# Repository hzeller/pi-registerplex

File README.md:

GPIO Multiplexer with registers
================================

 * 1x32 'raw' output of GPIO pins, or inputs if not used with a Pi
 * 1x32 bit buffer (AHCT245) to buffer all 28 GPIO bits plus 4 user bits
 * 2x32 bit registers (AHCT574) with user-choice of clock.
 * 6 NOT gates that can be used to use as clock inverter and play with gate
   delays.

This board directly plugs into the Rasbperry Pi and can be used as a GPIO
multiplexer with that, but the raw inputs are also available directly, so
this can be used in any project. The 34 pin connectors have the same
pinout throughout: +5V and GND followed by 32 bits of data.

Using the AHCT gates allows to voltage convert 3.3V logic levels to 5V.

The chip packages are [DHVQFN20], which allows for compact design and is
still somewhat easy to solder if you use a stencil.

Chip       | Package              | Vendor type example
-----------|----------------------|---------------
74AHCT245  | DHVQFN20 (SOT764-1)  | NXP 74AHCT245BQ,115
74AHCT574  | DHVQFN20 (SOT764-1)  | NXP 74AHCT574BQ,115
74AHCT04   | DHVQFN14 (SOT762-1)  | NXP 74AHCT04BQ,115

The clocks (`J6` and `J7`) of the registers are not connected by default, so
it allows you to choose any GPIO output or other signal to clock in the
registers.

The buffer and registers are for 32 bits, but we only have 28 GPIO outputs.
The remaining bits are passed through as user bits (`U1` ... `U4`) from inputs
on the `J2` 'Raw' header.

PCB is [shared on OshPark].

### Using two clocks
Pick two GPIO lines as a clock to connect to `J6` and `J7` allows to write
to the registers. Straight forward:

  1. write Datum1, transition clock2 `¯╲_`
  2. transition clock1 `_╱¯`  _(clocks in Datum1)_
  3. Write Datum2, transition clock1 `¯╲_`
  4. transition clock2 `_╱¯`  _(clocks in Datum2)_

In this case, the inverter gates are not needed.

### Using one clock
Chose one GPIO as clock and wire it up to an inverter. Wire up one of the 574's
directly to the pin, and the other through the inverter.

  1. Write Datum1
  2. transition clock `_╱¯` _(clocks in Datum1)_
  3. Write Datum2
  4. transition clock `¯╲_` _(the inverted signal clocks in Datum2)_

Same as above, but only one clock line needed.

### Danger zone: DDR with just two writes

Wire up the `Clock` line to at least one inverters, maybe more in one chain to
create some delay. Let's call this `Clock'`. Take the output of that through
another inverter, let's call this `Clock''`. Connect these to `J6` and `J7`.

 1. Clock in Datum1 and with it transition `Clock` `_╱¯`. The delayed
    clock prime that transitions to positive a few nanoseconds later will
    clock in the data.
 2. Clock in Datum2 and with it transition `Clock` `¯╲_`. The inverted clock
    from (1) now transitions to positive a few nanoseconds later
    will clock in the data.

Each write write will store one datum. Using the gates as
delay line and inverter, no separate cycle is needed, each swing of the
clock generates a store.

This is dangerous of course: it is not necessarily stable as we rely on the
delay to be long enough for the D-FlipFlops set-up time, and this will highly
depend on the chip manufacturer, temperature, age, ...
Maybe use RC + AHCT14 or LV14 Schmitt-Trigger for a more defined delay ?

[DHVQFN20]: https://www.nexperia.com/packages/SOT764-1.html
[shared on OshPark]: https://oshpark.com/shared_projects/xJGfE6Gh

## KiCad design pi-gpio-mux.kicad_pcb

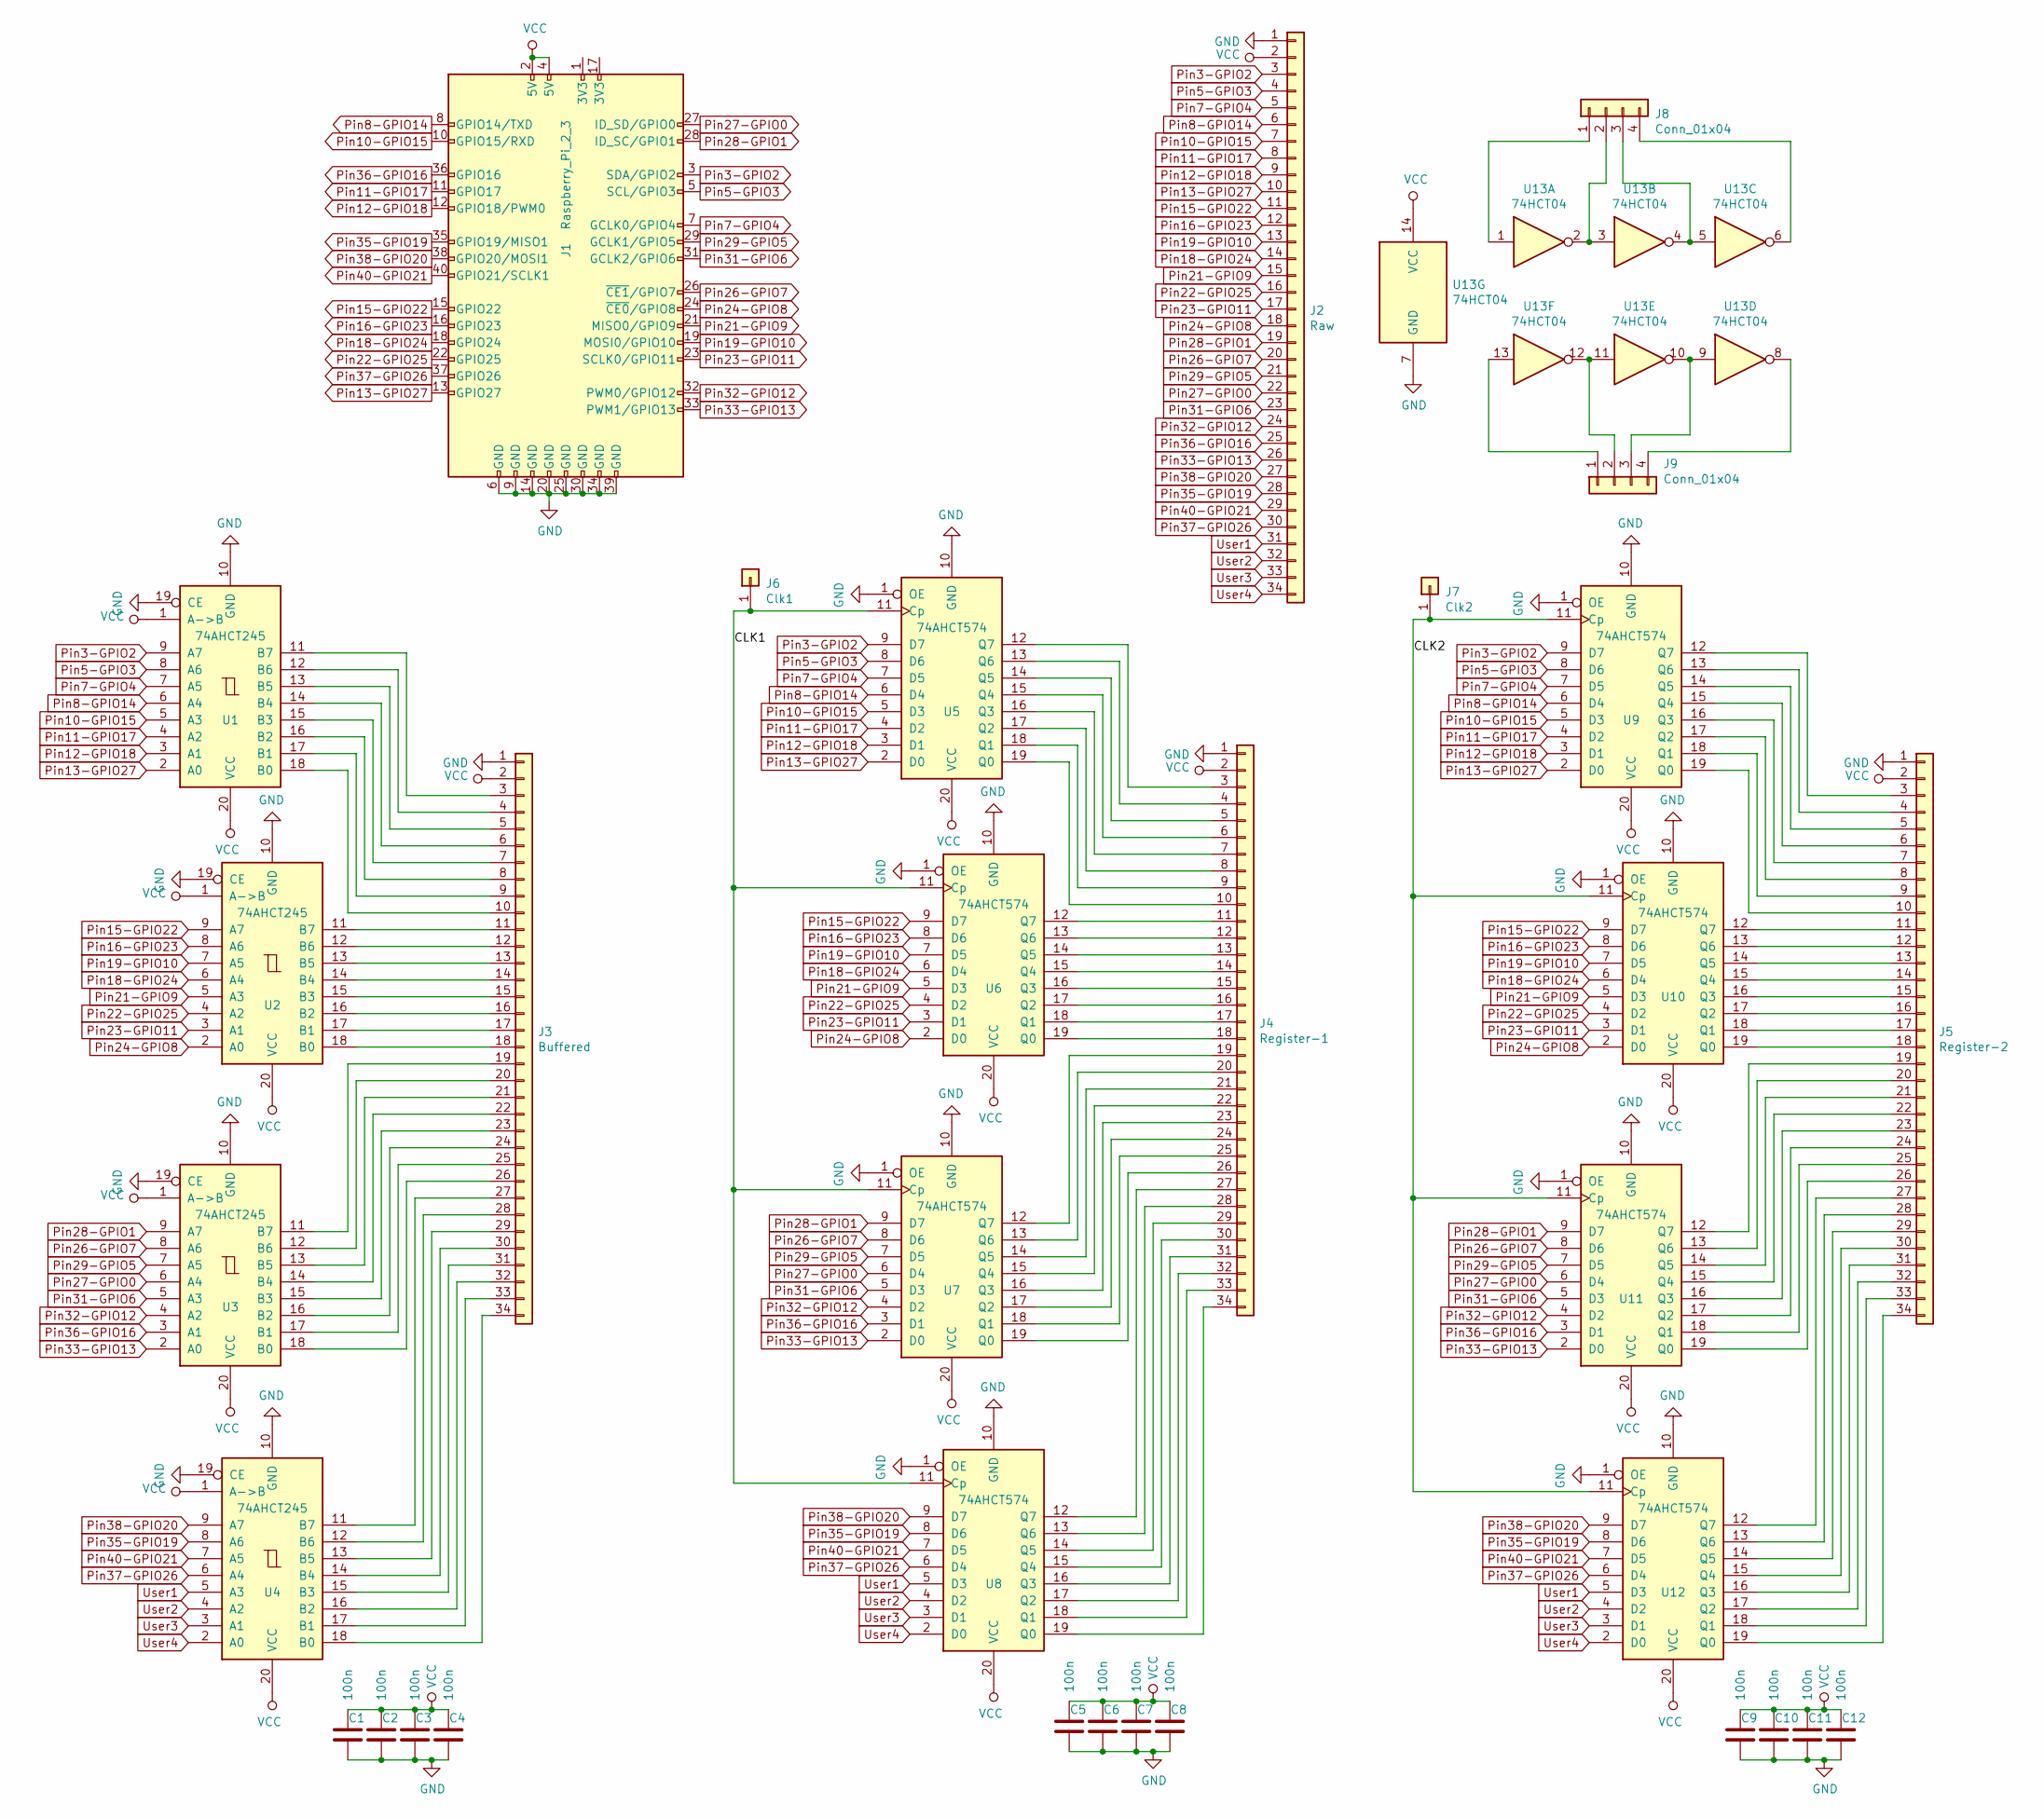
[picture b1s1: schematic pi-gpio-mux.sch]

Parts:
C1, C2, C3, C4, C5, C6, C7, C8, C9, C10, C11, C12: 100n; C_0603_1608Metric
J1: Raspberry_Pi_2_3; PinHeader_2x20_P2.54mm_Vertical
J2: Raw; IDC-GPIO
J3: Buffered; IDC-GPIO
J4: Register-1; IDC-GPIO
J5: Register-2; IDC-GPIO
J6: Clk1; Pin_D0.7mm_L6.5mm_W1.8mm_FlatFork
J7: Clk2; Pin_D0.7mm_L6.5mm_W1.8mm_FlatFork
J8, J9: Conn_01x04; triple-inverter
U1, U2, U3, U4: 74AHCT245; SOT764-1-DHVQFN20
U5, U6, U7, U8, U9, U10, U11, U12: 74AHCT574; SOT764-1-DHVQFN20
U13: 74HCT04; SOT762-1-DHVQFN14

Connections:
/CLK1: J6.1, U5.11 (Cp), U6.11 (Cp), U7.11 (Cp), U8.11 (Cp)
/CLK2: J7.1, U9.11 (Cp), U10.11 (Cp), U11.11 (Cp), U12.11 (Cp)
GND: C1.2, C2.2, C3.2, C4.2, C5.2, C6.2, C7.2, C8.2, C9.2, C10.2, C11.2, C12.2, J1.6 (GND), J1.9 (GND), J1.14 (GND), J1.20 (GND), J1.25 (GND), J1.30 (GND), J1.34 (GND), J1.39 (GND), J2.1, J3.1, J4.1, J5.1, U1.10 (GND), U1.19 (CE), U2.10 (GND), U2.19 (CE), U3.10 (GND), U3.19 (CE), U4.10 (GND), U4.19 (CE), U5.1 (OE), U5.10 (GND), U6.1 (OE), U6.10 (GND), U7.1 (OE), U7.10 (GND), U8.1 (OE), U8.10 (GND), U9.1 (OE), U9.10 (GND), U10.1 (OE), U10.10 (GND), U11.1 (OE), U11.10 (GND), U12.1 (OE), U12.10 (GND), U13.7 (GND)
unnamed: J3.3, U1.11 (B7)
unnamed: J3.4, U1.12 (B6)
unnamed: J3.5, U1.13 (B5)
unnamed: J3.6, U1.14 (B4)
unnamed: J3.7, U1.15 (B3)
unnamed: J3.8, U1.16 (B2)
unnamed: J3.9, U1.17 (B1)
unnamed: J3.10, U1.18 (B0)
unnamed: J3.11, U2.11 (B7)
unnamed: J3.12, U2.12 (B6)
unnamed: J3.13, U2.13 (B5)
unnamed: J3.14, U2.14 (B4)
unnamed: J3.15, U2.15 (B3)
unnamed: J3.16, U2.16 (B2)
unnamed: J3.17, U2.17 (B1)
unnamed: J3.18, U2.18 (B0)
unnamed: J3.19, U3.11 (B7)
unnamed: J3.20, U3.12 (B6)
unnamed: J3.21, U3.13 (B5)
unnamed: J3.22, U3.14 (B4)
unnamed: J3.23, U3.15 (B3)
unnamed: J3.24, U3.16 (B2)
unnamed: J3.25, U3.17 (B1)
unnamed: J3.26, U3.18 (B0)
unnamed: J3.27, U4.11 (B7)
unnamed: J3.28, U4.12 (B6)
unnamed: J3.29, U4.13 (B5)
unnamed: J3.30, U4.14 (B4)
unnamed: J3.31, U4.15 (B3)
unnamed: J3.32, U4.16 (B2)
unnamed: J3.33, U4.17 (B1)
unnamed: J3.34, U4.18 (B0)
unnamed: J4.3, U5.12 (Q7)
unnamed: J4.4, U5.13 (Q6)
unnamed: J4.5, U5.14 (Q5)
unnamed: J4.6, U5.15 (Q4)
unnamed: J4.7, U5.16 (Q3)
unnamed: J4.8, U5.17 (Q2)
unnamed: J4.9, U5.18 (Q1)
unnamed: J4.10, U5.19 (Q0)
unnamed: J4.11, U6.12 (Q7)
unnamed: J4.12, U6.13 (Q6)
unnamed: J4.13, U6.14 (Q5)
unnamed: J4.14, U6.15 (Q4)
unnamed: J4.15, U6.16 (Q3)
unnamed: J4.16, U6.17 (Q2)
unnamed: J4.17, U6.18 (Q1)
unnamed: J4.18, U6.19 (Q0)
unnamed: J4.19, U7.12 (Q7)
unnamed: J4.20, U7.13 (Q6)
unnamed: J4.21, U7.14 (Q5)
unnamed: J4.22, U7.15 (Q4)
unnamed: J4.23, U7.16 (Q3)
unnamed: J4.24, U7.17 (Q2)
unnamed: J4.25, U7.18 (Q1)
unnamed: J4.26, U7.19 (Q0)
unnamed: J4.27, U8.12 (Q7)
unnamed: J4.28, U8.13 (Q6)
unnamed: J4.29, U8.14 (Q5)
unnamed: J4.30, U8.15 (Q4)
unnamed: J4.31, U8.16 (Q3)
unnamed: J4.32, U8.17 (Q2)
unnamed: J4.33, U8.18 (Q1)
unnamed: J4.34, U8.19 (Q0)
unnamed: J5.3, U9.12 (Q7)
unnamed: J5.4, U9.13 (Q6)
unnamed: J5.5, U9.14 (Q5)
unnamed: J5.6, U9.15 (Q4)
unnamed: J5.7, U9.16 (Q3)
unnamed: J5.8, U9.17 (Q2)
unnamed: J5.9, U9.18 (Q1)
unnamed: J5.10, U9.19 (Q0)
unnamed: J5.11, U10.12 (Q7)
unnamed: J5.12, U10.13 (Q6)
unnamed: J5.13, U10.14 (Q5)
unnamed: J5.14, U10.15 (Q4)
unnamed: J5.15, U10.16 (Q3)
unnamed: J5.16, U10.17 (Q2)
unnamed: J5.17, U10.18 (Q1)
unnamed: J5.18, U10.19 (Q0)
unnamed: J5.19, U11.12 (Q7)
unnamed: J5.20, U11.13 (Q6)
unnamed: J5.21, U11.14 (Q5)
unnamed: J5.22, U11.15 (Q4)
unnamed: J5.23, U11.16 (Q3)
unnamed: J5.24, U11.17 (Q2)
unnamed: J5.25, U11.18 (Q1)
unnamed: J5.26, U11.19 (Q0)
unnamed: J5.27, U12.12 (Q7)
unnamed: J5.28, U12.13 (Q6)
unnamed: J5.29, U12.14 (Q5)
unnamed: J5.30, U12.15 (Q4)
unnamed: J5.31, U12.16 (Q3)
unnamed: J5.32, U12.17 (Q2)
unnamed: J5.33, U12.18 (Q1)
unnamed: J5.34, U12.19 (Q0)
unnamed: J8.1, U13.1
unnamed: J8.2, U13.2, U13.3
unnamed: J8.3, U13.4, U13.5
unnamed: J8.4, U13.6
unnamed: J9.1, U13.13
unnamed: J9.2, U13.11, U13.12
unnamed: J9.3, U13.9, U13.10
unnamed: J9.4, U13.8
Pin3-GPIO2: J1.3 (SDA/GPIO2), J2.3, U1.9 (A7), U5.9 (D7), U9.9 (D7)
Pin5-GPIO3: J1.5 (SCL/GPIO3), J2.4, U1.8 (A6), U5.8 (D6), U9.8 (D6)
Pin7-GPIO4: J1.7 (GCLK0/GPIO4), J2.5, U1.7 (A5), U5.7 (D5), U9.7 (D5)
Pin8-GPIO14: J1.8 (GPIO14/TXD), J2.6, U1.6 (A4), U5.6 (D4), U9.6 (D4)
Pin10-GPIO15: J1.10 (GPIO15/RXD), J2.7, U1.5 (A3), U5.5 (D3), U9.5 (D3)
Pin11-GPIO17: J1.11 (GPIO17), J2.8, U1.4 (A2), U5.4 (D2), U9.4 (D2)
Pin12-GPIO18: J1.12 (GPIO18/PWM0), J2.9, U1.3 (A1), U5.3 (D1), U9.3 (D1)
Pin13-GPIO27: J1.13 (GPIO27), J2.10, U1.2 (A0), U5.2 (D0), U9.2 (D0)
Pin15-GPIO22: J1.15 (GPIO22), J2.11, U2.9 (A7), U6.9 (D7), U10.9 (D7)
Pin16-GPIO23: J1.16 (GPIO23), J2.12, U2.8 (A6), U6.8 (D6), U10.8 (D6)
Pin18-GPIO24: J1.18 (GPIO24), J2.14, U2.6 (A4), U6.6 (D4), U10.6 (D4)
Pin19-GPIO10: J1.19 (MOSI0/GPIO10), J2.13, U2.7 (A5), U6.7 (D5), U10.7 (D5)
Pin21-GPIO9: J1.21 (MISO0/GPIO9), J2.15, U2.5 (A3), U6.5 (D3), U10.5 (D3)
Pin22-GPIO25: J1.22 (GPIO25), J2.16, U2.4 (A2), U6.4 (D2), U10.4 (D2)
Pin23-GPIO11: J1.23 (SCLK0/GPIO11), J2.17, U2.3 (A1), U6.3 (D1), U10.3 (D1)
Pin24-GPIO8: J1.24 (~CE0~/GPIO8), J2.18, U2.2 (A0), U6.2 (D0), U10.2 (D0)
Pin26-GPIO7: J1.26 (~CE1~/GPIO7), J2.20, U3.8 (A6), U7.8 (D6), U11.8 (D6)
Pin27-GPIO0: J1.27 (ID_SD/GPIO0), J2.22, U3.6 (A4), U7.6 (D4), U11.6 (D4)
Pin28-GPIO1: J1.28 (ID_SC/GPIO1), J2.19, U3.9 (A7), U7.9 (D7), U11.9 (D7)
Pin29-GPIO5: J1.29 (GCLK1/GPIO5), J2.21, U3.7 (A5), U7.7 (D5), U11.7 (D5)
Pin31-GPIO6: J1.31 (GCLK2/GPIO6), J2.23, U3.5 (A3), U7.5 (D3), U11.5 (D3)
Pin32-GPIO12: J1.32 (PWM0/GPIO12), J2.24, U3.4 (A2), U7.4 (D2), U11.4 (D2)
Pin33-GPIO13: J1.33 (PWM1/GPIO13), J2.26, U3.2 (A0), U7.2 (D0), U11.2 (D0)
Pin35-GPIO19: J1.35 (GPIO19/MISO1), J2.28, U4.8 (A6), U8.8 (D6), U12.8 (D6)
Pin36-GPIO16: J1.36 (GPIO16), J2.25, U3.3 (A1), U7.3 (D1), U11.3 (D1)
Pin37-GPIO26: J1.37 (GPIO26), J2.30, U4.6 (A4), U8.6 (D4), U12.6 (D4)
Pin38-GPIO20: J1.38 (GPIO20/MOSI1), J2.27, U4.9 (A7), U8.9 (D7), U12.9 (D7)
Pin40-GPIO21: J1.40 (GPIO21/SCLK1), J2.29, U4.7 (A5), U8.7 (D5), U12.7 (D5)
User1: J2.31, U4.5 (A3), U8.5 (D3), U12.5 (D3)
User2: J2.32, U4.4 (A2), U8.4 (D2), U12.4 (D2)
User3: J2.33, U4.3 (A1), U8.3 (D1), U12.3 (D1)
User4: J2.34, U4.2 (A0), U8.2 (D0), U12.2 (D0)
VCC: C1.1, C2.1, C3.1, C4.1, C5.1, C6.1, C7.1, C8.1, C9.1, C10.1, C11.1, C12.1, J1.2 (5V), J1.4 (5V), J2.2, J3.2, J4.2, J5.2, U1.1 (A->B), U1.20 (VCC), U2.1 (A->B), U2.20 (VCC), U3.1 (A->B), U3.20 (VCC), U4.1 (A->B), U4.20 (VCC), U5.20 (VCC), U6.20 (VCC), U7.20 (VCC), U8.20 (VCC), U9.20 (VCC), U10.20 (VCC), U11.20 (VCC), U12.20 (VCC), U13.14 (VCC)

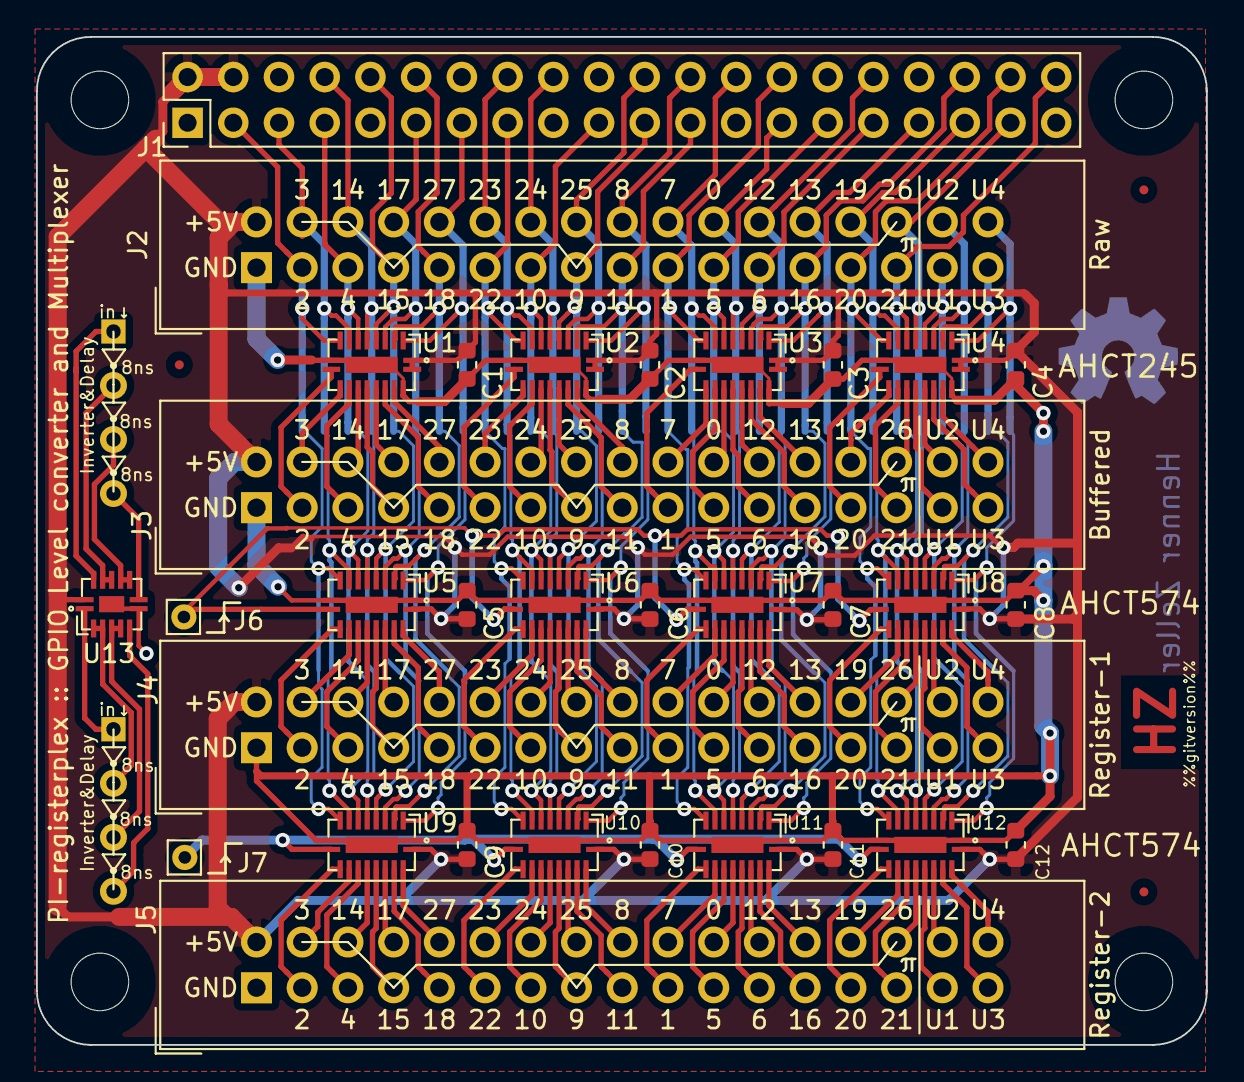
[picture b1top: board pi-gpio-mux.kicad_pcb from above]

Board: 2 copper layers, 65.0 x 56.0 mm, 34 parts (0 on the bottom side), 140 nets.

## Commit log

2019-07-20 Start buffered and latch GPIO board for the Pi.
2019-07-20 Even placement.
2019-07-20 Basic fan-out.
2019-07-20 First layout template vias.
2019-07-20 Replicate template.
2019-07-20 Power and clock routing for Registers.
2019-07-20 trace signal between connectors.
2019-07-20 Bus connect between registers.
2019-07-20 Bus raw -> registers.
2019-07-20 Bus raw -> buffers
2019-07-20 Start power connections.
2019-07-20 remove info cache; not needed.
2019-07-20 Even length of initial bus traces on copper side.
2019-07-20 Solve routing of VCC for buffers.
2019-07-21 Route VCC and GND. No unrouted left.
2019-07-21 Add inverters.
2019-07-21 More copper clearance around screw holes; add VCC pour on top layer.
2019-07-21 Improve 1 marker packages; add %%gitversion%% and Makefile to create fab.
2019-07-21 Add simple readme.
2019-07-21 Add schematic picture to README.
2019-07-21 Make sure to base the %%gitversion%% only on the kicad_pcb version.
2019-07-22 Add Fiducials.
2019-07-22 Use opportunity to add another ground trace in parallel to existing in reg2.
    Also: re-route an inverter trace to allow non-interrupted flow of VCC copper
    around clock pad.
2019-07-23 Slightly lower impedance for a couple VCC/GND traces.
2019-07-29 Show outline of chips on silk-screen.
2019-07-29 Update README.
2020-08-08 Refine README.
